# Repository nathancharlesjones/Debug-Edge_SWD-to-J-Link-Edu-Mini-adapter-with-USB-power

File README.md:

# Debug Edge adapter: SWD to J-Link Edu Mini with USB power

## What is it?

This PCB is an adapter board which is intended to connect a J-Link Edu Mini with a board-to-board connector made by AVX; it also includes a USB connector and voltage regulator in order to optionally provide power to the MCU being debugged. This allows MCU boards to be made which require no additional hardware in order to connect to a debugger and which need only a very small footprint in order to make that connection.

This project was inspired by and drew heavily from the [Debug Edge](https://debug-edge.io/) project. You can read more about the uses of this adapter there.

## How do I order it?

A set of Gerber files is included in this repo as a .zip file. You can submit that to any PCB manufacturer for assembly, though it was designed with JLC PCB in mind and follows their [capabilities](https://jlcpcb.com/capabilities/Capabilities).

You'll also need the following parts, at a minimum:
- 1x AVX 6-pin board-to-board connector, part #009159006061916 ([link to product page on Mouser](https://www.mouser.com/ProductDetail/581-009159006061916/))
- 1x 2x5 terminal strip, 0.05" spacing, PTH (ex: Samtec FTSH-105-01-F-D ([link to product page on Mouser](https://www.mouser.com/ProductDetail/200-FTSH10501FD/)))

If you intend to use USB power, you'll also need the following:
- 1x USB mini-B connector (ex: TE 2172034-1 ([link to product page on Digi-Key](https://www.digikey.com/en/products/detail/2172034-1/A135698-ND/5592056?utm_medium=email&utm_source=oce&utm_campaign=3480_OCE21RT&utm_content=productdetail_US&utm_cid=624598&so=67827782&mkt_tok=eyJpIjoiTWpZM1lqSmlZV1kxWVdJdyIsInQiOiI5RGVuOWlmdVwvY3A1NUsxSUlRa1JiZXkrRnJ4dUJ5YldFTDV4bkxUUGhPTkJHT29cL0pBWHpTa3dnV3FXbDA1S2szRDduaEw1Y21VYndoeElrdUZTRlNZcFwvOWpSaG1lMW9DeDRqTFFKNXBGQ2x5VEdwRFlncmJzdW1NYmVmWG51RyJ9)))
- 1x 3.3V regulator, TO-92 (ex: Microchip MCP1700-3302 ([link to product page on Digi-Key](https://www.digikey.com/en/products/detail/MCP1700-3302E%2fTO/MCP1700-3302E%2fTO-ND/652680?utm_medium=email&utm_source=oce&utm_campaign=3480_OCE21RT&utm_content=productdetail_US&utm_cid=624598&so=67827782&mkt_tok=eyJpIjoiTWpZM1lqSmlZV1kxWVdJdyIsInQiOiI5RGVuOWlmdVwvY3A1NUsxSUlRa1JiZXkrRnJ4dUJ5YldFTDV4bkxUUGhPTkJHT29cL0pBWHpTa3dnV3FXbDA1S2szRDduaEw1Y21VYndoeElrdUZTRlNZcFwvOWpSaG1lMW9DeDRqTFFKNXBGQ2x5VEdwRFlncmJzdW1NYmVmWG51RyJ9)))
  - You may use any value voltage regulator you'd like, but keep in mind that the silkscreen will not match if you choose to do so.
- 2x 1uF capacitors, PTH
- 1x 1x3 0.1" male headers
- 1x Jumper

## How do I use it?

First, you'll need a PCB which has been designed to be used with the Debug Edge adapter. You can find an example of another PCB that I laid out which includes the Debug Edge adapter [here](https://github.com/nathancharlesjones/STM32F103C8T6-breakout-board/).

After assembling this PCB, use the AVX connector to mate the MCU PCB with the adapter board. Connect one end of a 10-pin cable to J3 and the other to a debug adapter such as the Segger J-Link Edu Mini. If you are using USB power, also connect a USB mini-B cable to J4 and place a jumper over the correct voltage you'd like to use to power the MCU, either 5V or 3.3V (or, possibly, another voltage if you've chosen a different voltage regulator).

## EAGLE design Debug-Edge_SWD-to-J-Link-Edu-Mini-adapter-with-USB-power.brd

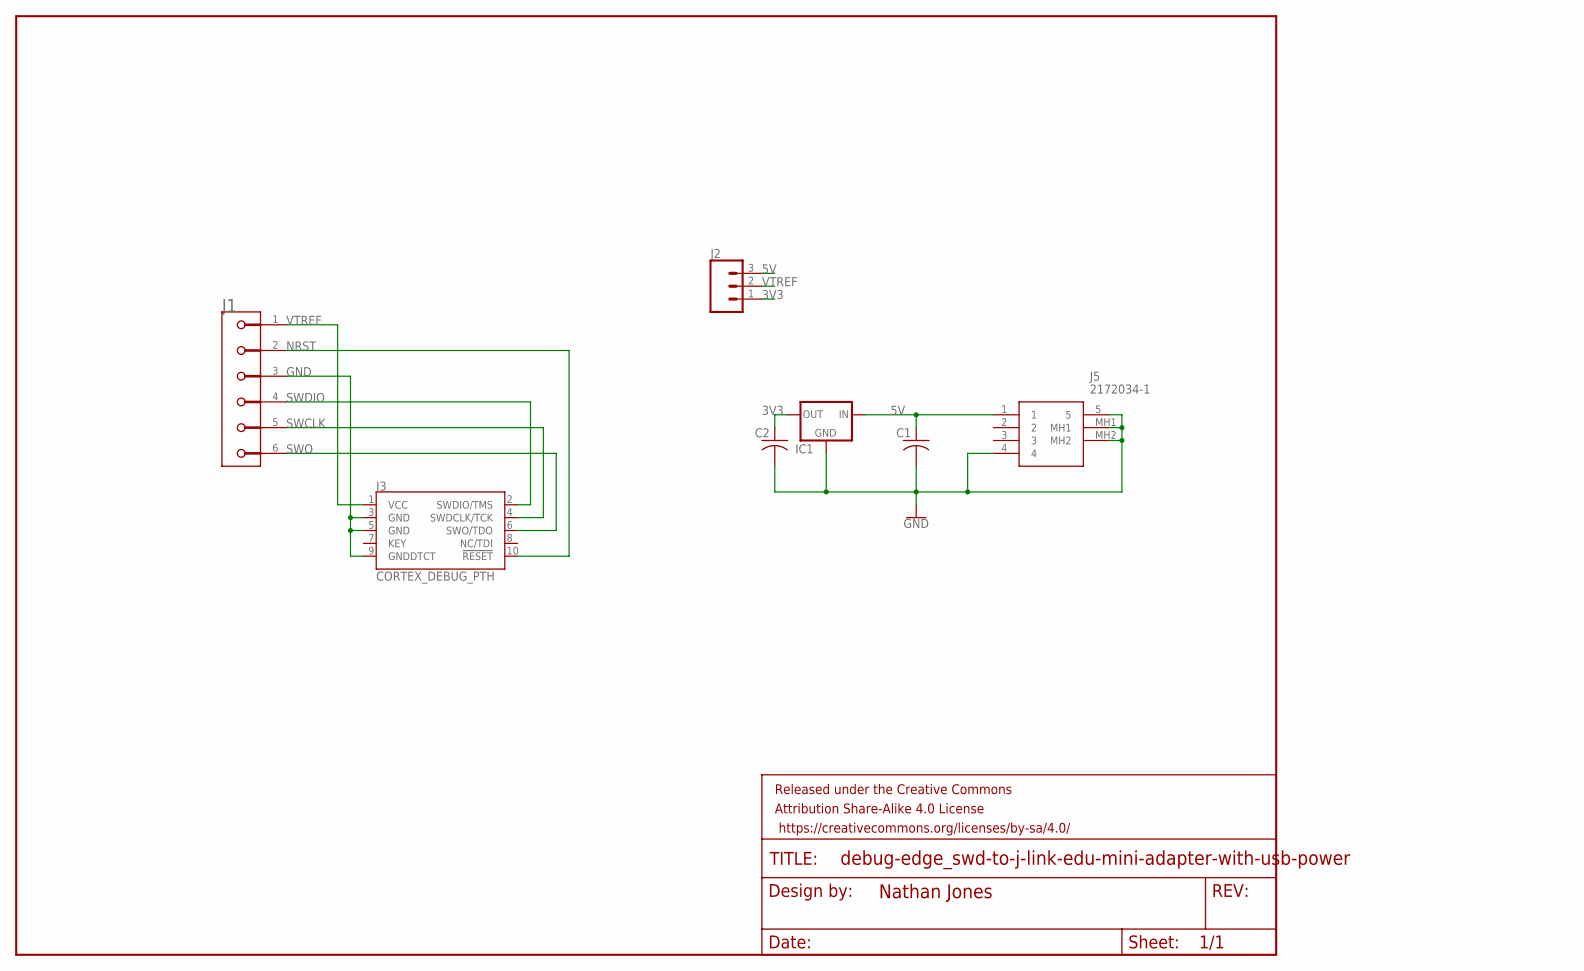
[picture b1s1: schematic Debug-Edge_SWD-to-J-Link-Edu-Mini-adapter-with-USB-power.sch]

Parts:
C1, C2: C-US025-024X044; C025-024X044
FRAME1: FRAME-LETTERNO_PACKAGE; DUMMY
IC1: MCP1700INLINE; TO92-INLINE
J1: AVX_6-PIN_009159006061916; AVX_6-PIN_009159006061916_0
J2: CONN_031X03_NO_SILK; 1X03_NO_SILK
J3: CORTEX_DEBUG_PTH; 2X5-PTH-1.27MM
J5: 2172034-1; 21720341

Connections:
3V3: C2.1, IC1.3 (OUT), J2.1
5V: C1.1, IC1.2 (IN), J2.3, J5.1
GND: C1.2, C2.2, IC1.1 (GND), J1.3, J3.3 (GND), J3.5 (GND), J3.9 (GNDDTCT), J5.4, J5.5, J5.MH1, J5.MH2
NRST: J1.2, J3.10 (!RESET)
SWCLK: J1.5, J3.4 (SWDCLK/TCK)
SWDIO: J1.4, J3.2 (SWDIO/TMS)
SWO: J1.6, J3.6 (SWO/TDO)
VTREF: J1.1, J2.2, J3.1 (VCC)

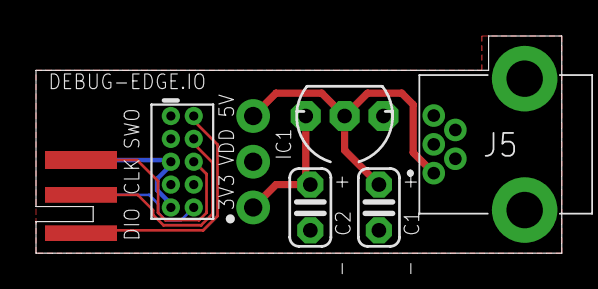
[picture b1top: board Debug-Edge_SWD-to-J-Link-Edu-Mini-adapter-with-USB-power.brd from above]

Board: 2 copper layers, 29.2 x 12.1 mm, 8 parts (1 on the bottom side), 8 nets.

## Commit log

2021-01-02 Adding files.
2021-01-05 Updated README. Added PCB images.
2021-01-05 Updated README.
2021-01-30 Updated AVX library. Changed to PTH components.
2021-01-30 Updated images.
2021-01-30 Updated Gerber.
2021-01-31 Added design block.
2021-02-05 Updated footprint for USB connector.
2021-02-05 Updated PCB images.

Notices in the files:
parts and their libraries:
SparkFun-Connectors: Licensing: Creative Commons ShareAlike 4.0 International - https://creativecommons.org/licenses/by-sa/4.0
SparkFun-Aesthetics: Released under the Creative Commons Attribution Share-Alike 4.0 License
SparkFun-Aesthetics: https://creativecommons.org/licenses/by-sa/4.0
